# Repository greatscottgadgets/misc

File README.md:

misc
====

miscellaneous Great Scott Gadgets projects

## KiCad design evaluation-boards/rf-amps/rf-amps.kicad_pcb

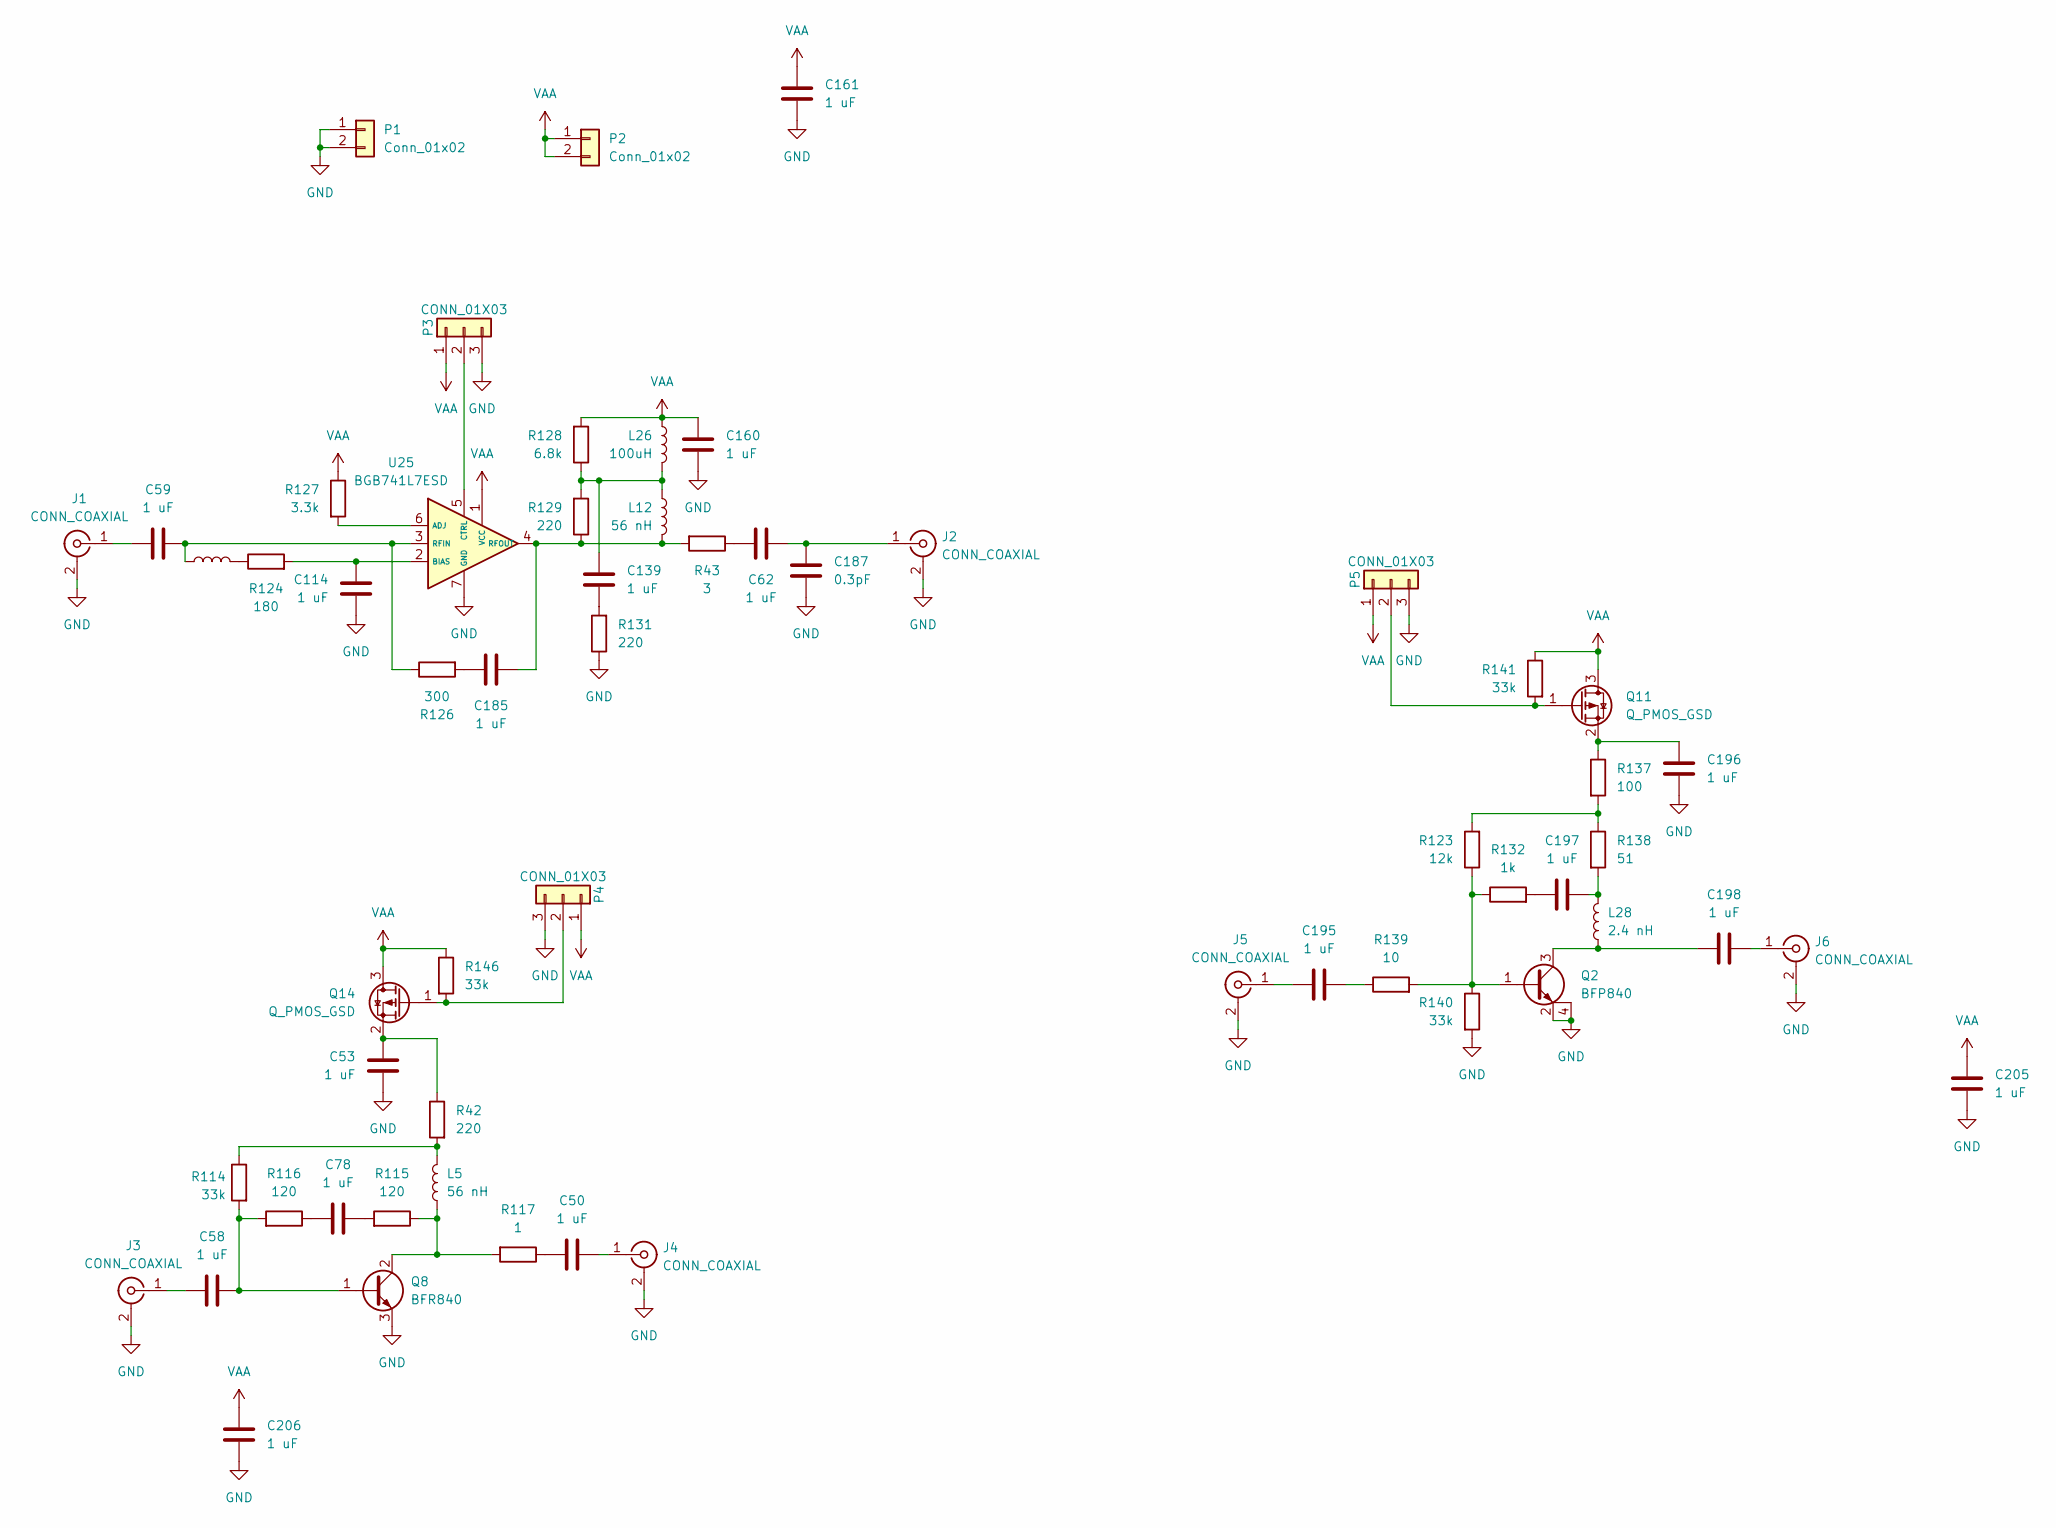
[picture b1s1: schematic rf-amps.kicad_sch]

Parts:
C50, C53, C58, C59, C62, C78, C114, C139, C160, C161, C185, C195, C196, C197, C198, C205, C206: 1 uF; C_0201_0603Metric; Part Number GRM033R61A105ME44D
C187: 0.3pF; C_0201_0603Metric; Part Number GRM0335C1ER30BA01D
J1, J2, J3, J4, J5, J6: CONN_COAXIAL; SMA_MyAntenna_A-SMA-KE-16.5A_EdgeMount
L5, L12: 56 nH; L_0201_0603Metric; Part Number LQP03TN56NJ02D
L25: 8.2 nH; L_0201_0603Metric; Part Number LQP03TN8N2J02D
L26: 100uH; L_TDK_MLZ2012_h1.25mm; Part Number MLZ2012N101LT000
L28: 2.4 nH; L_0201_0603Metric; Part Number LQP03TN2N4C02D
P1, P2: Conn_01x02; PinHeader_1x02_P2.54mm_Vertical
P3, P4, P5: CONN_01X03; PinHeader_1x03_P2.54mm_Vertical
Q2: BFP840; SOT-343-4-3; Part Number BFP840ESDH6327XTSA1
Q8: BFR840; TSLP-3-9; Part Number BFR840L3RHESDE6327XTSA1
Q11, Q14: Q_PMOS_GSD; TSLP-3-9; Part Number LP0404N3T5G
R42, R129, R131: 220; R_0201_0603Metric; Part Number RC0201JR-07220RL
R43: 3; R_0201_0603Metric; Part Number RC0402JR-073RL
R114, R140, R141, R146: 33k; R_0201_0603Metric; Part Number RC0201JR-0733KL
R115, R116: 120; R_0201_0603Metric; Part Number RC0201FR-07120RL
R117: 1; R_0201_0603Metric; Part Number RC0201JR-071RL
R123: 12k; R_0201_0603Metric; Part Number RC0201FR-0712KL
R124: 180; R_0201_0603Metric; Part Number RC0201FR-07180RL
R126: 300; R_0201_0603Metric; Part Number RC0201FR-07300RL
R127: 3.3k; R_0201_0603Metric; Part Number RC0201FR-073K3L
R128: 6.8k; R_0201_0603Metric; Part Number RC0201FR-076K8L
R132: 1k; R_0201_0603Metric; Part Number RC0201FR-071KL
R137: 100; R_0201_0603Metric; Part Number RC0201JR-07100RL
R138: 51; R_0201_0603Metric; Part Number RC0201JR-0751RL
R139: 10; R_0201_0603Metric; Part Number RC0201JR-0710RL
U25: BGB741L7ESD; TSLP-7-1; Part Number BGB741L7ESDE6327XTSA1

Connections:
GND: C53.2, C114.2, C160.2, C161.2, C187.2, C196.2, C205.2, C206.2, J1.2 (Ext), J2.2 (Ext), J3.2 (Ext), J4.2 (Ext), J5.2 (Ext), J6.2 (Ext), P1.1, P1.2, P3.3, P4.3, P5.3, Q2.2 (E), Q2.4 (C), Q8.3 (E), R131.1, R140.2, U25.7 (GND)
unnamed: C50.2, R117.1
unnamed: C62.1, R43.1
unnamed: C78.1, R115.2
unnamed: C78.2, R116.1
unnamed: C139.1, L12.1, L26.2, R128.1, R129.2
unnamed: C139.2, R131.2
unnamed: C185.2, R126.2
unnamed: C195.1, R139.1
unnamed: C197.1, L28.2, R138.2
unnamed: C197.2, R132.2
unnamed: C198.2, L28.1, Q2.3 (C)
unnamed: C59.1, J1.1 (In)
unnamed: C62.2, C187.1, J2.1 (In)
unnamed: C58.1, J3.1 (In)
unnamed: C50.1, J4.1 (In)
unnamed: C195.2, J5.1 (In)
unnamed: C198.1, J6.1 (In)
unnamed: L5.1, R42.2, R114.1
unnamed: L25.2, R124.1
unnamed: P3.2, U25.5 (CTRL)
unnamed: P4.2, Q14.1 (G), R146.2
unnamed: P5.2, Q11.1 (G), R141.2
unnamed: Q2.1 (B), R123.1, R132.1, R139.2, R140.1
unnamed: C58.2, Q8.1 (B), R114.2, R116.2
unnamed: L5.2, Q8.2 (C), R115.1, R117.2
unnamed: C196.1, Q11.2 (S), R137.1
unnamed: C53.1, Q14.2 (S), R42.1
unnamed: R123.2, R137.2, R138.1
unnamed: R127.2, U25.6 (ADJ)
unnamed: C114.1, R124.2, U25.2 (BIAS)
unnamed: C59.2, L25.1, R126.1, U25.3 (RFIN)
unnamed: C185.1, L12.2, R43.2, R129.1, U25.4 (RFOUT)
VAA: C160.1, C161.1, C205.1, C206.1, L26.1, P2.1, P2.2, P3.1, P4.1, P5.1, Q11.3 (D), Q14.3 (D), R127.1, R128.2, R141.1, R146.1, U25.1 (VCC)

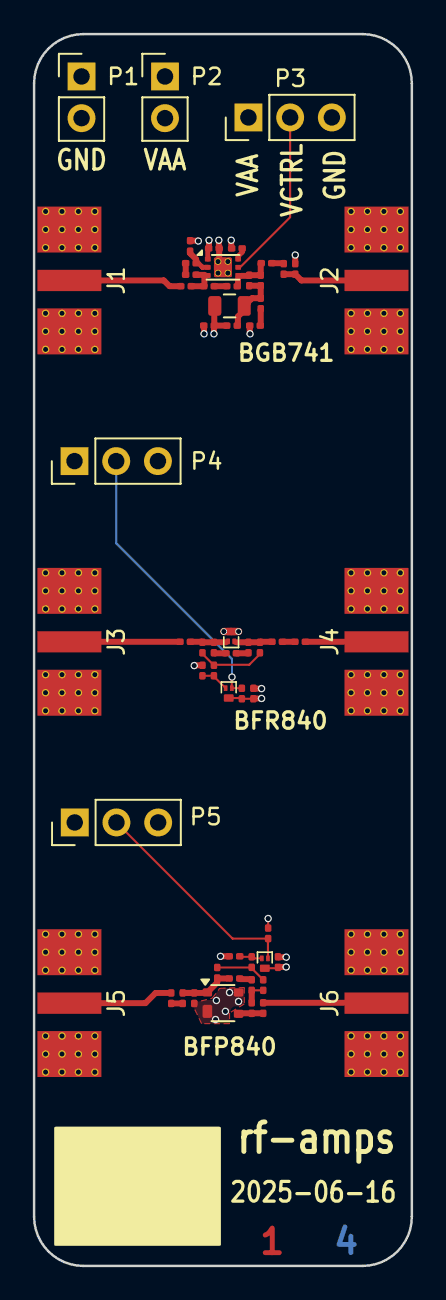
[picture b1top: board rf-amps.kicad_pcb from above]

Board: 4 copper layers, 23.0 x 75.0 mm, 59 parts (0 on the bottom side), 34 nets.

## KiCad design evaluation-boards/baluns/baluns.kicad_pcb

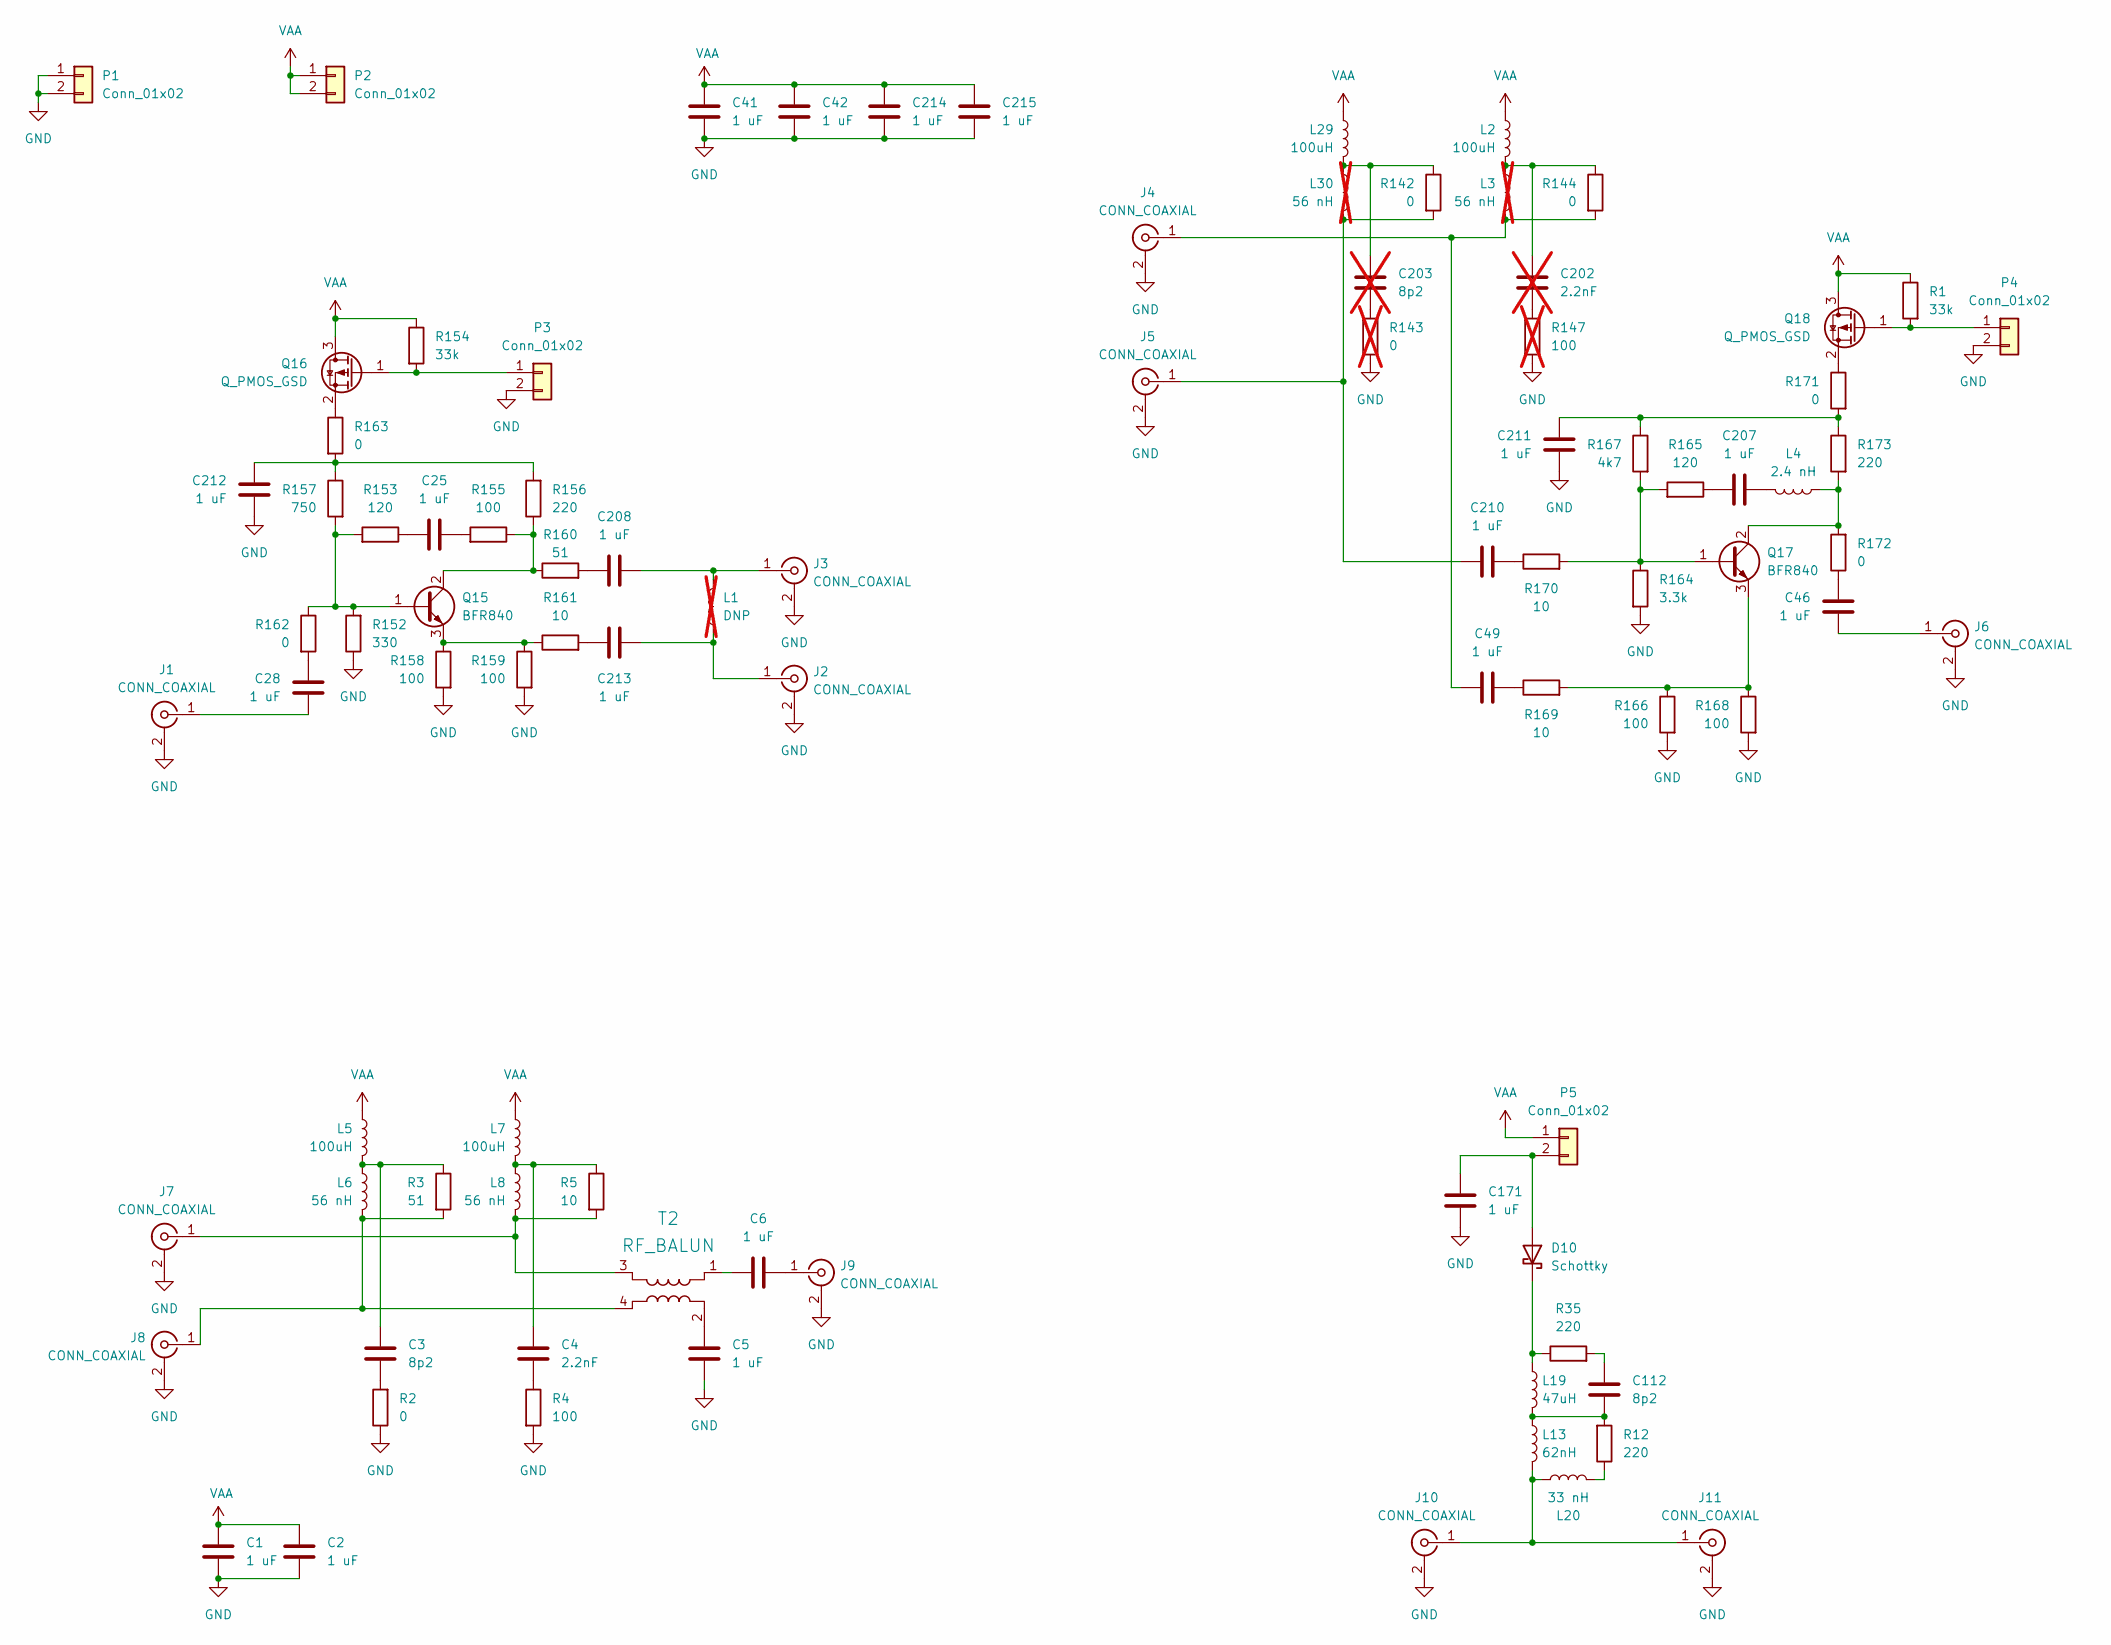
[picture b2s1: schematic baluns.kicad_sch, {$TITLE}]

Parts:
C1, C2, C5, C6, C25, C28, C41, C42, C46, C49, C171, C207, C208, C210, C211, C212, C213, C214, C215: 1 uF; C_0201_0603Metric; Part Number GRM033R61A105ME44D
C3, C112: 8p2; C_0201_0603Metric; Part Number GRM0335C1H8R2CA01D
C4: 2.2nF; C_0201_0603Metric; Part Number GRM033R71A222KA01D
C202: 2.2nF; C_0201_0603Metric; Part Number GRM033R71A222KA01D; not fitted
C203: 8p2; C_0201_0603Metric; Part Number GRM0335C1H8R2CA01D; not fitted
D10: Schottky; TSLP-2-19; Part Number PMEG4010ESBYL
J1, J2, J3, J4, J5, J6, J7, J8, J9, J10, J11: CONN_COAXIAL; SMA_MyAntenna_A-SMA-KE-16.5A_EdgeMount
L1: DNP; L_0201_0603Metric; not fitted
L2, L5, L7, L29: 100uH; L_TDK_MLZ2012_h1.25mm; Part Number MLZ2012N101LT000
L3, L30: 56 nH; L_0201_0603Metric; Part Number LQP03TN56NJ02D; not fitted
L4: 2.4 nH; L_0201_0603Metric; Part Number LQP03TN2N4C02D
L6, L8: 56 nH; L_0201_0603Metric; Part Number LQP03TN56NJ02D
L13: 62nH; L_0603_1608Metric; Part Number LQW18AN62NJ00D
L19: 47uH; L_Taiyo-Yuden_A251818; Part Number LSQEA251818T470M
L20: 33 nH; L_0201_0603Metric; Part Number LQP03TN33NJ02D
P1, P2, P3, P4, P5: Conn_01x02; PinHeader_1x02_P2.54mm_Vertical
Q15, Q17: BFR840; TSLP-3-9; Part Number BFR840L3RHESDE6327XTSA1
Q16, Q18: Q_PMOS_GSD; TSLP-3-9; Part Number LP0404N3T5G
R1, R154: 33k; R_0201_0603Metric; Part Number RC0201JR-0733KL
R2, R142, R144, R162, R163, R171, R172: 0; R_0201_0603Metric; Part Number RC0201JR-070RL
R3, R160: 51; R_0201_0603Metric; Part Number RC0201JR-0751RL
R4, R155, R158, R159, R166, R168: 100; R_0201_0603Metric; Part Number RC0201JR-07100RL
R5, R161, R169, R170: 10; R_0201_0603Metric; Part Number RC0201JR-0710RL
R12, R35, R156, R173: 220; R_0201_0603Metric; Part Number RC0201JR-07220RL
R143: 0; R_0201_0603Metric; Part Number RC0201JR-070RL; not fitted
R147: 100; R_0201_0603Metric; Part Number RC0201JR-07100RL; not fitted
R152: 330; R_0201_0603Metric; Part Number RC0201JR-07330RL
R153, R165: 120; R_0201_0603Metric; Part Number RC0201FR-07120RL
R157: 750; R_0201_0603Metric; Part Number RC0201JR-07750RL
R164: 3.3k; R_0201_0603Metric; Part Number RC0201FR-073K3L
R167: 4k7; R_0201_0603Metric; Part Number RC0201FR-074K7L
T2: RF_BALUN; Anaren_0805_2012Metric-6; Part Number B0310J50100AHF

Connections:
GND: C1.2, C2.2, C5.1, C41.2, C42.2, C171.2, C211.2, C212.2, C214.2, C215.2, J1.2 (Ext), J2.2 (Ext), J3.2 (Ext), J4.2 (Ext), J5.2 (Ext), J6.2 (Ext), J7.2 (Ext), J8.2 (Ext), J9.2 (Ext), J10.2 (Ext), J11.2 (Ext), P1.1, P1.2, P3.2, P4.2, R2.1, R4.2, R143.1, R147.2, R152.1, R158.2, R159.2, R164.2, R166.2, R168.2
unnamed: C3.1, L5.2, L6.1, R3.1
unnamed: C3.2, R2.2
unnamed: C4.1, R4.1
unnamed: C4.2, L7.2, L8.1, R5.1
unnamed: C6.2, T2.1
unnamed: C25.1, R155.2
unnamed: C25.2, R153.1
unnamed: C28.1, R162.2
unnamed: C46.1, R172.1
unnamed: C49.1, R169.1
unnamed: C112.1, R35.2
unnamed: C112.2, L13.1, L19.2, R12.2
unnamed: C202.1, R147.1
unnamed: C202.2, L2.2, L3.1, R144.1
unnamed: C203.1, L29.2, L30.1, R142.1
unnamed: C203.2, R143.2
unnamed: C207.1, L4.2
unnamed: C207.2, R165.1
unnamed: C208.2, R160.2
unnamed: C210.1, R170.1
unnamed: C211.1, R167.1, R171.2, R173.1
unnamed: C212.1, R156.2, R157.1, R163.2
unnamed: C213.2, R161.2
unnamed: C171.1, D10.2 (A), P5.2
unnamed: D10.1 (K), L19.1, R35.1
unnamed: C28.2, J1.1 (In)
unnamed: C213.1, J2.1 (In), L1.1
unnamed: C208.1, J3.1 (In), L1.2
unnamed: C49.2, J4.1 (In), L3.2, R144.2
unnamed: C210.2, J5.1 (In), L30.2, R142.2
unnamed: C46.2, J6.1 (In)
unnamed: J7.1 (In), L8.2, R5.2, T2.3
unnamed: J8.1 (In), L6.2, R3.2, T2.4
unnamed: C6.1, J9.1 (In)
unnamed: J10.1 (In), J11.1 (In), L13.2, L20.2
unnamed: L20.1, R12.1
unnamed: P3.1, Q16.1 (G), R154.2
unnamed: P4.1, Q18.1 (G), R1.2
unnamed: Q15.1 (B), R152.2, R153.2, R157.2, R162.1
unnamed: Q15.2 (C), R155.1, R156.1, R160.1
unnamed: Q15.3 (E), R158.1, R159.1, R161.1
unnamed: Q16.2 (S), R163.1
unnamed: Q17.1 (B), R164.1, R165.2, R167.2, R170.2
unnamed: L4.1, Q17.2 (C), R172.2, R173.2
unnamed: Q17.3 (E), R166.1, R168.1, R169.2
unnamed: Q18.2 (S), R171.1
unnamed: C5.2, T2.2 (GND)
VAA: C1.1, C2.1, C41.1, C42.1, C214.1, C215.1, L2.1, L5.1, L7.1, L29.1, P2.1, P2.2, P5.1, Q16.3 (D), Q18.3 (D), R1.1, R154.1

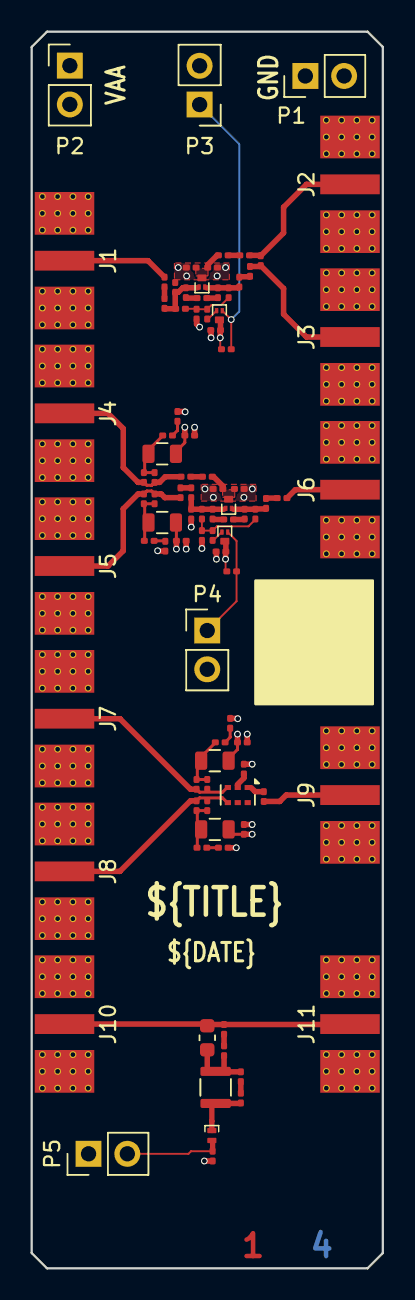
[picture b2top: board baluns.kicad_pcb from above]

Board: 4 copper layers, 23.0 x 81.0 mm, 92 parts (0 on the bottom side), 49 nets.

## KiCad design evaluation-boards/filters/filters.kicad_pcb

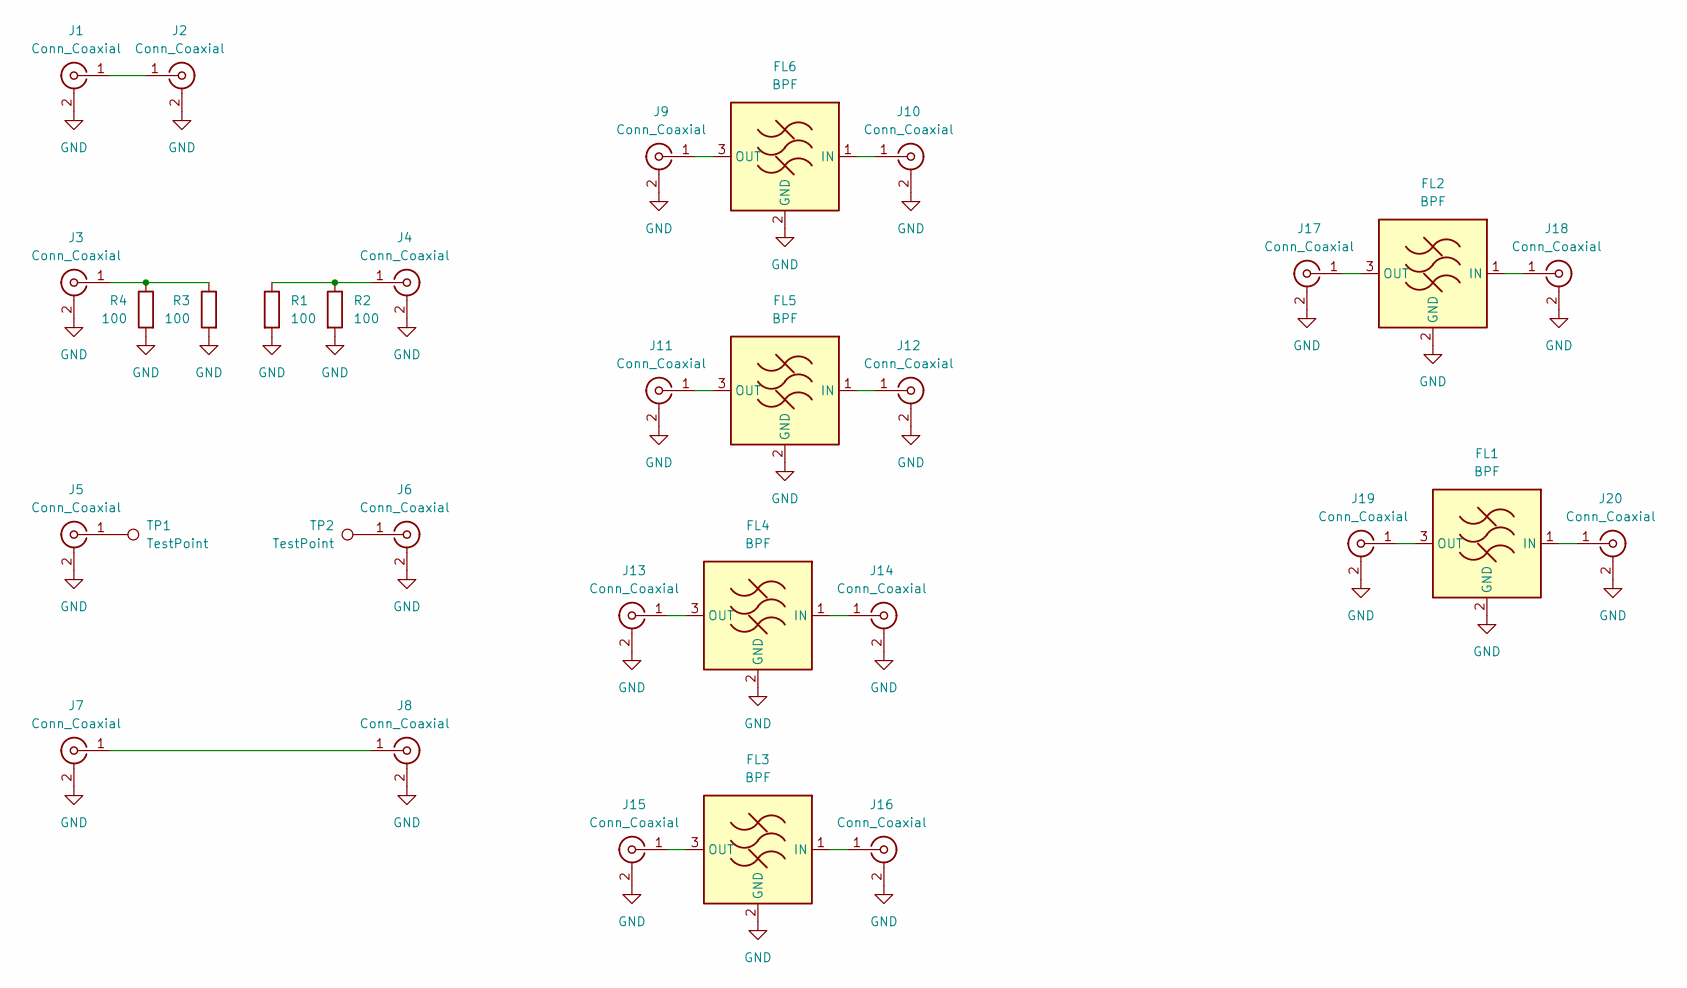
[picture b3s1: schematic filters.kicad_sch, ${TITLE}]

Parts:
FL1, FL2, FL3, FL4, FL5, FL6: BPF; Filter_Pulse_BPF1608LM09R5000A; Part Number BPF1608LM02R2400A
J1, J2, J3, J4, J5, J6, J7, J8, J9, J10, J11, J12, J13, J14, J15, J16, J17, J18, J19, J20: Conn_Coaxial; SMA_MyAntenna_A-SMA-KE-16.5A_EdgeMount
R1, R2, R3, R4: 100; R_0201_0603Metric
TP1, TP2: TestPoint; Square_Pad_0.364x0.364mm

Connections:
GND: FL1.2 (GND), FL1.4 (GND), FL2.2 (GND), FL2.4 (GND), FL3.2 (GND), FL3.4 (GND), FL4.2 (GND), FL4.4 (GND), FL5.2 (GND), FL5.4 (GND), FL6.2 (GND), FL6.4 (GND), J1.2 (Ext), J2.2 (Ext), J3.2 (Ext), J4.2 (Ext), J5.2 (Ext), J6.2 (Ext), J7.2 (Ext), J8.2 (Ext), J9.2 (Ext), J10.2 (Ext), J11.2 (Ext), J12.2 (Ext), J13.2 (Ext), J14.2 (Ext), J15.2 (Ext), J16.2 (Ext), J17.2 (Ext), J18.2 (Ext), J19.2 (Ext), J20.2 (Ext), R1.2, R2.2, R3.2, R4.2
unnamed: FL1.1 (IN), J20.1 (In)
unnamed: FL1.3 (OUT), J19.1 (In)
unnamed: FL2.1 (IN), J18.1 (In)
unnamed: FL2.3 (OUT), J17.1 (In)
unnamed: FL3.1 (IN), J16.1 (In)
unnamed: FL3.3 (OUT), J15.1 (In)
unnamed: FL4.1 (IN), J14.1 (In)
unnamed: FL4.3 (OUT), J13.1 (In)
unnamed: FL5.1 (IN), J12.1 (In)
unnamed: FL5.3 (OUT), J11.1 (In)
unnamed: FL6.1 (IN), J10.1 (In)
unnamed: FL6.3 (OUT), J9.1 (In)
unnamed: J1.1 (In), J2.1 (In)
unnamed: J3.1 (In), R3.1, R4.1
unnamed: J4.1 (In), R1.1, R2.1
unnamed: J5.1 (In), TP1.1
unnamed: J6.1 (In), TP2.1
unnamed: J7.1 (In), J8.1 (In)

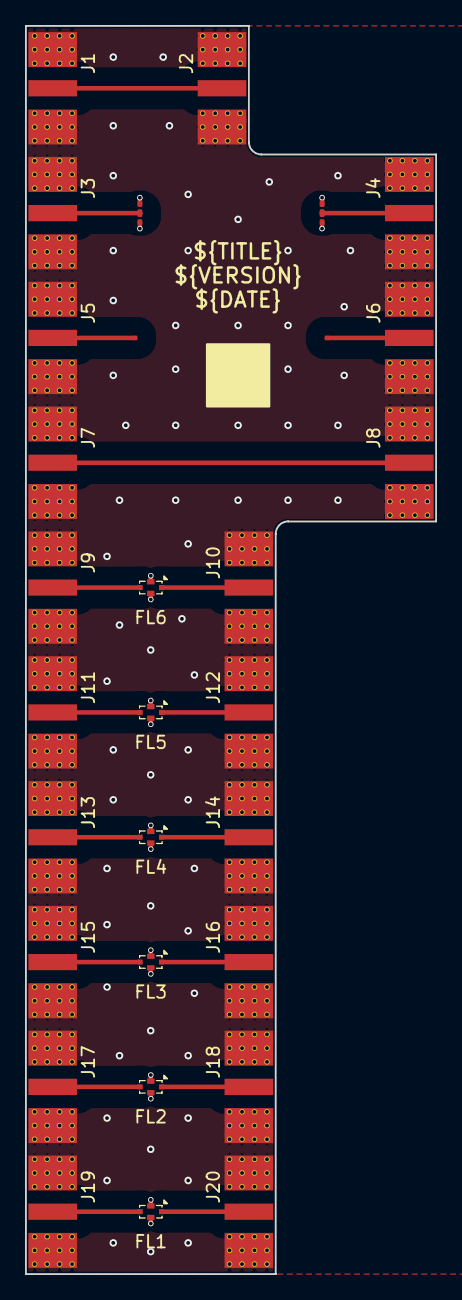
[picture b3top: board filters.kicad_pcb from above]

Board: 4 copper layers, 32.9 x 100.0 mm, 32 parts (0 on the bottom side), 19 nets.

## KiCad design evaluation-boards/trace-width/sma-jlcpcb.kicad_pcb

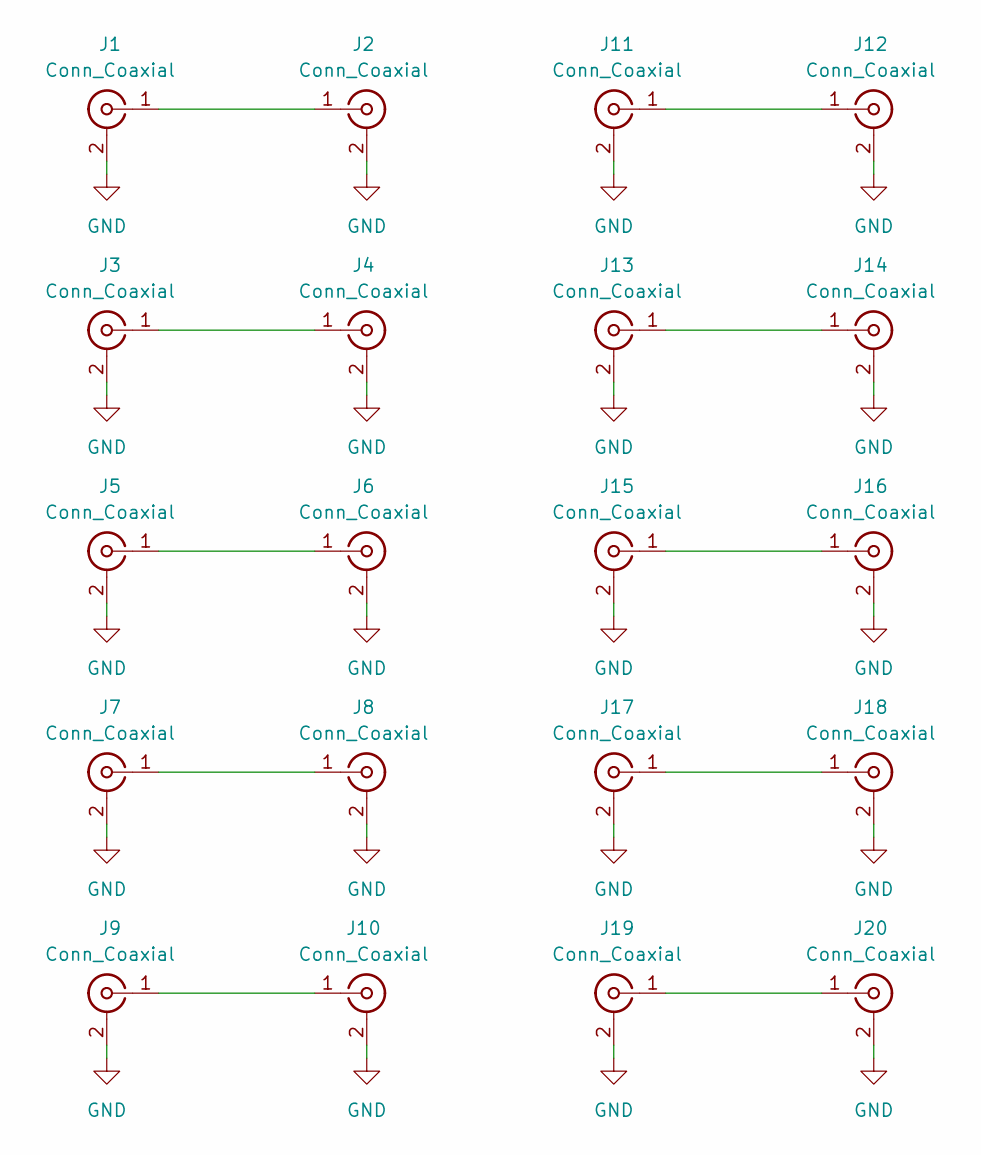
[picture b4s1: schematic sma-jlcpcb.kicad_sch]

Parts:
J1, J2, J3, J4, J5, J6, J7, J8, J9, J10, J11, J12, J13, J14, J15, J16, J17, J18, J19, J20: Conn_Coaxial

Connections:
GND: J1.2 (Ext), J2.2 (Ext), J3.2 (Ext), J4.2 (Ext), J5.2 (Ext), J6.2 (Ext), J7.2 (Ext), J8.2 (Ext), J9.2 (Ext), J10.2 (Ext), J11.2 (Ext), J12.2 (Ext), J13.2 (Ext), J14.2 (Ext), J15.2 (Ext), J16.2 (Ext), J17.2 (Ext), J18.2 (Ext), J19.2 (Ext), J20.2 (Ext)
unnamed: J1.1 (In), J2.1 (In)
unnamed: J3.1 (In), J4.1 (In)
unnamed: J5.1 (In), J6.1 (In)
unnamed: J7.1 (In), J8.1 (In)
unnamed: J9.1 (In), J10.1 (In)
unnamed: J11.1 (In), J12.1 (In)
unnamed: J13.1 (In), J14.1 (In)
unnamed: J15.1 (In), J16.1 (In)
unnamed: J17.1 (In), J18.1 (In)
unnamed: J19.1 (In), J20.1 (In)

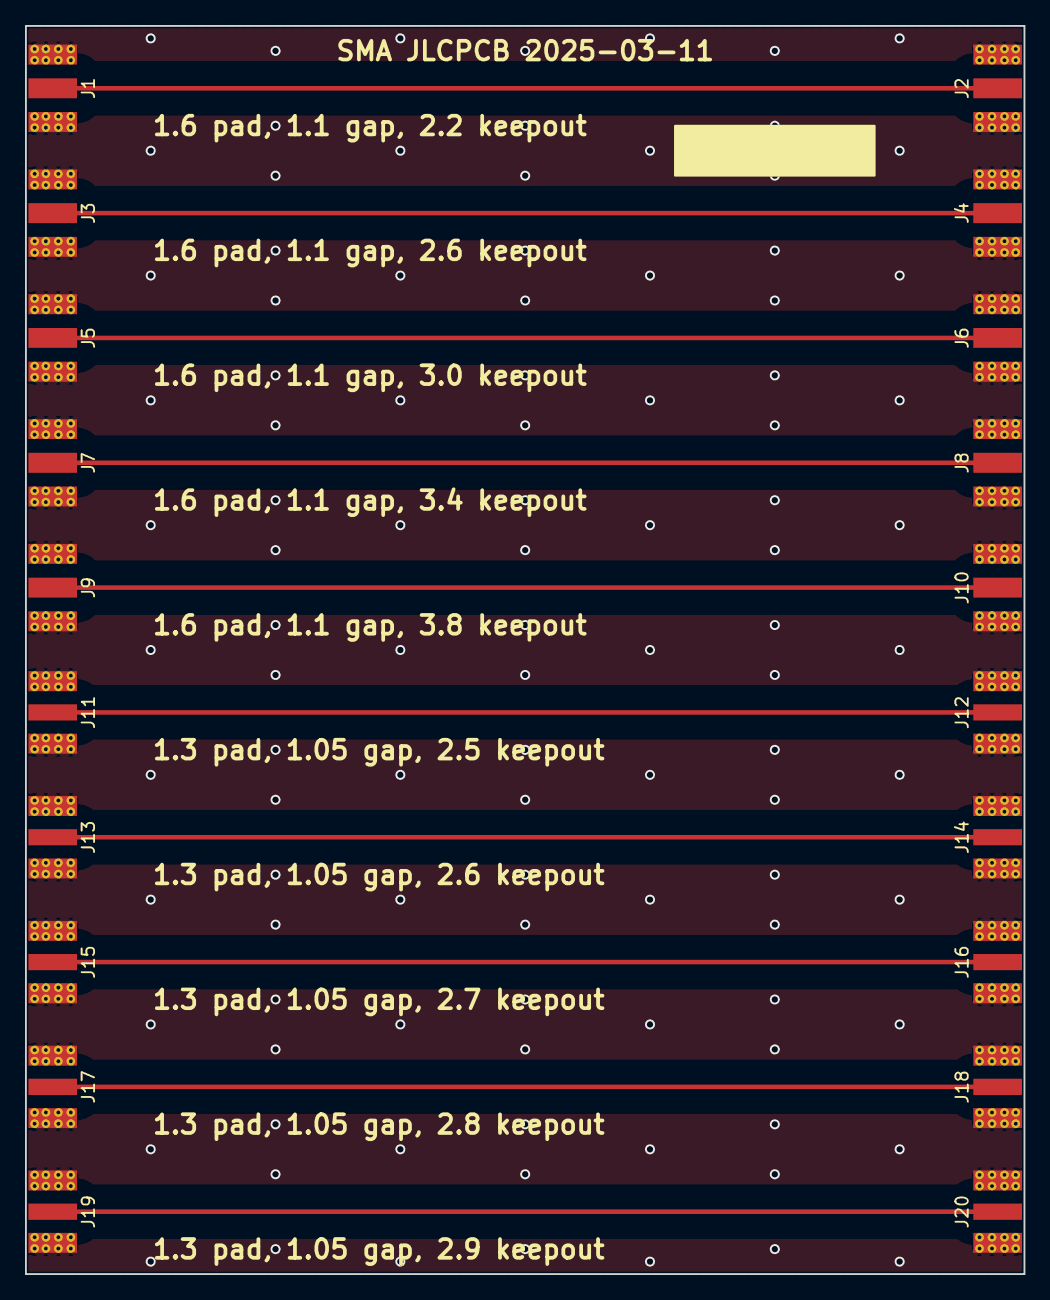
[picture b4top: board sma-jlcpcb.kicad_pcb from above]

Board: 6 copper layers, 80.0 x 100.0 mm, 20 parts (0 on the bottom side), 11 nets.

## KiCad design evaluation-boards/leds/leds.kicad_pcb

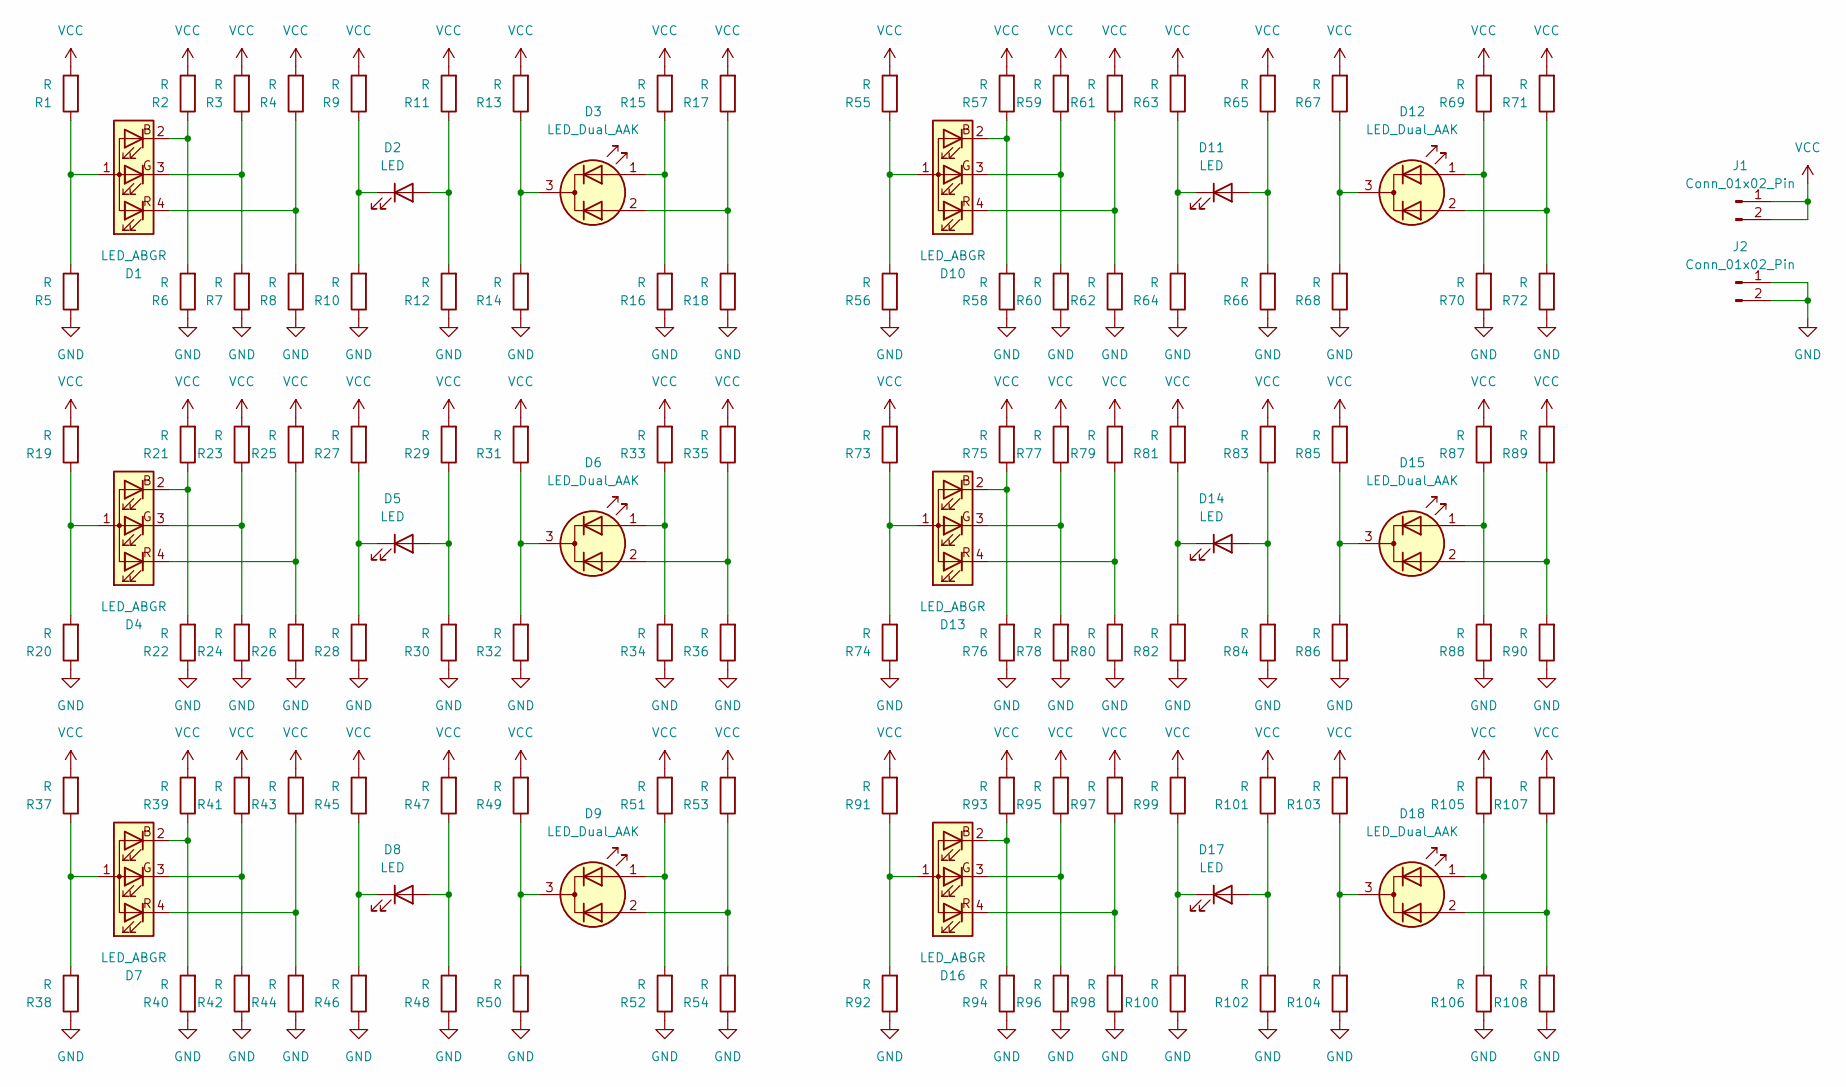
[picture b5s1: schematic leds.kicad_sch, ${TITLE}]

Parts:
D1, D4, D7, D10, D13, D16: LED_ABGR; LED_RGB_Everlight_EASV3015RGBA0_Horizontal
D2, D5, D8, D11, D14, D17: LED; LED_Kingbright_APA1606_1.6x0.6mm_Horizontal
D3, D6, D9, D12, D15, D18: LED_Dual_AAK; LED_Kingbright_KPA-3010_3x2x1mm
J1, J2: Conn_01x02_Pin; PinHeader_1x02_P2.54mm_Vertical
R1, R2, R3, R4, R5, R6, R7, R8, R9, R10, R11, R12, R13, R14, R15, R16, R17, R18, R19, R20, R21, R22, R23, R24, R25, R26, R27, R28, R29, R30, R31, R32, R33, R34, R35, R36, R37, R38, R39, R40, R41, R42, R43, R44, R45, R46, R47, R48, R49, R50, R51, R52, R53, R54, R55, R56, R57, R58, R59, R60, R61, R62, R63, R64, R65, R66, R67, R68, R69, R70, R71, R72, R73, R74, R75, R76, R77, R78, R79, R80, R81, R82, R83, R84, R85, R86, R87, R88, R89, R90, R91, R92, R93, R94, R95, R96, R97, R98, R99, R100, R101, R102, R103, R104, R105, R106, R107, R108: R; R_0402_1005Metric

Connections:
GND: J2.1, J2.2, R5.1, R6.1, R7.1, R8.1, R10.1, R12.1, R14.1, R16.1, R18.1, R20.1, R22.1, R24.1, R26.1, R28.1, R30.1, R32.1, R34.1, R36.1, R38.1, R40.1, R42.1, R44.1, R46.1, R48.1, R50.1, R52.1, R54.1, R56.1, R58.1, R60.1, R62.1, R64.1, R66.1, R68.1, R70.1, R72.1, R74.1, R76.1, R78.1, R80.1, R82.1, R84.1, R86.1, R88.1, R90.1, R92.1, R94.1, R96.1, R98.1, R100.1, R102.1, R104.1, R106.1, R108.1
unnamed: D1.1 (A), R1.1, R5.2
unnamed: D1.2 (BK), R2.1, R6.2
unnamed: D1.3 (GK), R3.1, R7.2
unnamed: D1.4 (RK), R4.1, R8.2
unnamed: D2.2 (A), R11.1, R12.2
unnamed: D2.1 (K), R9.1, R10.2
unnamed: D3.1 (A1), R15.1, R16.2
unnamed: D3.2 (A2), R17.1, R18.2
unnamed: D3.3 (K), R13.1, R14.2
unnamed: D4.1 (A), R19.1, R20.2
unnamed: D4.2 (BK), R21.1, R22.2
unnamed: D4.3 (GK), R23.1, R24.2
unnamed: D4.4 (RK), R25.1, R26.2
unnamed: D5.2 (A), R29.1, R30.2
unnamed: D5.1 (K), R27.1, R28.2
unnamed: D6.1 (A1), R33.1, R34.2
unnamed: D6.2 (A2), R35.1, R36.2
unnamed: D6.3 (K), R31.1, R32.2
unnamed: D7.1 (A), R37.1, R38.2
unnamed: D7.2 (BK), R39.1, R40.2
unnamed: D7.3 (GK), R41.1, R42.2
unnamed: D7.4 (RK), R43.1, R44.2
unnamed: D8.2 (A), R47.1, R48.2
unnamed: D8.1 (K), R45.1, R46.2
unnamed: D9.1 (A1), R51.1, R52.2
unnamed: D9.2 (A2), R53.1, R54.2
unnamed: D9.3 (K), R49.1, R50.2
unnamed: D10.1 (A), R55.1, R56.2
unnamed: D10.2 (BK), R57.1, R58.2
unnamed: D10.3 (GK), R59.1, R60.2
unnamed: D10.4 (RK), R61.1, R62.2
unnamed: D11.2 (A), R65.1, R66.2
unnamed: D11.1 (K), R63.1, R64.2
unnamed: D12.1 (A1), R69.1, R70.2
unnamed: D12.2 (A2), R71.1, R72.2
unnamed: D12.3 (K), R67.1, R68.2
unnamed: D13.1 (A), R73.1, R74.2
unnamed: D13.2 (BK), R75.1, R76.2
unnamed: D13.3 (GK), R77.1, R78.2
unnamed: D13.4 (RK), R79.1, R80.2
unnamed: D14.2 (A), R83.1, R84.2
unnamed: D14.1 (K), R81.1, R82.2
unnamed: D15.1 (A1), R87.1, R88.2
unnamed: D15.2 (A2), R89.1, R90.2
unnamed: D15.3 (K), R85.1, R86.2
unnamed: D16.1 (A), R91.1, R92.2
unnamed: D16.2 (BK), R93.1, R94.2
unnamed: D16.3 (GK), R95.1, R96.2
unnamed: D16.4 (RK), R97.1, R98.2
unnamed: D17.2 (A), R101.1, R102.2
unnamed: D17.1 (K), R99.1, R100.2
unnamed: D18.1 (A1), R105.1, R106.2
unnamed: D18.2 (A2), R107.1, R108.2
unnamed: D18.3 (K), R103.1, R104.2
VCC: J1.1, J1.2, R1.2, R2.2, R3.2, R4.2, R9.2, R11.2, R13.2, R15.2, R17.2, R19.2, R21.2, R23.2, R25.2, R27.2, R29.2, R31.2, R33.2, R35.2, R37.2, R39.2, R41.2, R43.2, R45.2, R47.2, R49.2, R51.2, R53.2, R55.2, R57.2, R59.2, R61.2, R63.2, R65.2, R67.2, R69.2, R71.2, R73.2, R75.2, R77.2, R79.2, R81.2, R83.2, R85.2, R87.2, R89.2, R91.2, R93.2, R95.2, R97.2, R99.2, R101.2, R103.2, R105.2, R107.2

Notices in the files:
parts and their libraries:
COPYRIGHT: Copyright 2012-2025 Great Scott Gadgets
LICENSE: Licensed under the CERN-OHL-P v2
COPYRIGHT: Copyright 2024-2025 Great Scott Gadgets
COPYRIGHT: Copyright 2025 Great Scott Gadgets
COPYRIGHT: Copyright 2024 Great Scott Gadgets
